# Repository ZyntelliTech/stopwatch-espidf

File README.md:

# Stopwatch ESP-IDF Project

This project implements a stopwatch using ESP-IDF on an ESP32 microcontroller with an OLED display.
## Hardware Architecture
The ESP32-S3 GPIO pins have been assigned as follows: 

GPIO12 ------> SCL <br>
GPIO11 ------> SDA <br> 
GPIO10 ------> CS <br>
GPIO9  ------> DC<br>
GPIO8  ------> RES<br>

GPIO5  ------> left button: Start/Stop <br>
GPIOP6 ------> middle button: lapping/page navigation <br>
GPIO7  ------> right button: reset<br>

You can check the details in the schematic.

### How to order prototypes in JLCPCB
- Go to jlcpcb.com
- Click "Order now"
- Click "Add Gerber file" and upload /Hardware/Gerber_xxxxxxx.zip file
- Select the PCB Qty
- Enable the PCB Assembly
- Choose the Standard and Top Side assembly
- Click the NEXT button in the right panel. You will go to the next page
- Add the BOM and CPL(Pick-and-Place) files from hardware directory
- You can check the component stocks in the list
- In the Component Placements, you can check the assembled board.
- You can check the price in the Quote & Order page and save to cart

## Firmware Development

### Prerequisites

- [Visual Studio Code](https://code.visualstudio.com/)
- ESP32 development board (e.g., ESP32-S3)
- USB cable for flashing

### Installing ESP-IDF in VS Code

Follow these steps to set up the ESP-IDF development environment in Visual Studio Code. [Refer to this link.](https://www.youtube.com/watch?v=D0fRc4XHBNk) 

### 1. Install Visual Studio Code
If you haven't already, download and install VS Code from the official website.

### 2. Install the ESP-IDF Extension
1. Open VS Code.
2. Go to the Extensions view by clicking on the Extensions icon in the Activity Bar on the side of the window (or press `Ctrl+Shift+X`).
3. Search for "ESP-IDF".
4. Find the extension published by "Espressif Systems" and click "Install".

### 3. Open the Project
1. Open VS Code.
2. Select "File" > "Open Folder" and navigate to the `stopwatch-espidf/Firmware` directory.

### 4. Build and Flash the Project
1. In VS Code, open the Command Palette (`Ctrl+Shift+P`).
2. Type "ESP-IDF: Open ESP-IDF Terminal" and click it
3. Run "idf.py build".
4. Connect your ESP32 board via USB.
5. Run "idf.py flash monitor" to flash the firmware.
6. Optionally, run "idf.py -p COM[X] flash monitor" if the COM port is not automatically selected

## Project Structure

- `Firmware/`: Contains the ESP-IDF project files.
- `Firmware/main/`: Source code for the stopwatch application.
- `Firmware/components/`: Additional components like u8g2 for OLED display.
- `images/`: Project images like testing board diagram

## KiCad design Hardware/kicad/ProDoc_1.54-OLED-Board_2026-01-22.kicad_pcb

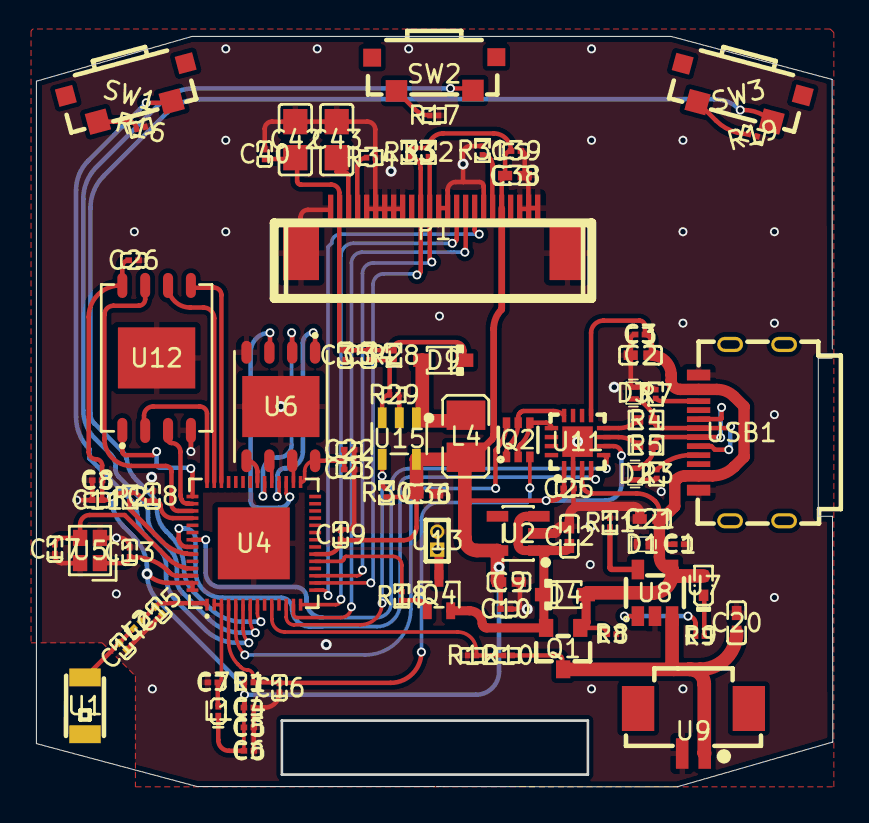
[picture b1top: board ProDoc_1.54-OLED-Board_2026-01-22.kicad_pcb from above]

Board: 2 copper layers, 44.2 x 41.7 mm, 83 parts (0 on the bottom side), 61 nets.

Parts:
C1: 2.2uF; C0201
C2, C9, C12, C20, C21, C36, C38: 10uF; C0402
C3, C4, C6, C7, C8, C10, C11, C16, C18, C19, C22, C25, C26, C35, C39, C40: 100nF; C0201
C5, C23: 1uF; C0201
C13, C17: 15pF; C0201
C14: 1.8pF; C0201
C15: 1.2pF; C0201
C34: 22pF; C0201
C42, C43: 10uF; C0805
D1, D2, D3: LESD8LH5.0CT5G; SOD-882_L1.0-W0.6-BI
D4, D9: 1N5819WS_C191023; SOD-323_L1.8-W1.3-LS2.5-RD
L1: 2nH; L0201-RD
L2: 2.4nH; L0201
L4: 10uH; L1008
P1: FPC 0.5MM 24P Pull type H2.0mm Pick up; FPC-SMD_24P-L17.5-W5.4-P0.50
Q1: AO3401A_C347476; SOT-23_L2.9-W1.3-P1.90-LS2.4-BR
Q2: UMH3N; SC-70-6_L2.2-W1.3-P0.65-LS2.1-BR
Q4: SS8550W; SOT-323-3_L2.0-W1.3-P1.30-LS2.3-BR
R1, R2, R16, R17, R19: 10kΩ; R0201
R3, R7: 5.1kΩ; R0201
R4, R5: 0Ω; R0402
R8, R29, R30: 100kΩ; R0201
R9: 1kΩ; R0201
R10, R12: 470kΩ; R0201
R11: 2kΩ; R0201
R18: 470Ω; R0201
R28: 887kΩ; R0201
R31, R32, R33: 4.7kΩ; R0201
R34: 910kΩ; R0201
SW1, SW2, SW3: TS36CA-0.6 250gf 031; SW-SMD_SHOU_TS36CA-0.6
U1: ANT3216LL00R2400A; ANT-SMD_L3.2-W1.6
U2: SPX3819M5-L-3-3; SOT-23-5_L3.0-W1.6-P0.95-LS2.8-BR
U4: ESP32-S3R8; QFN-56_L7.0-W7.0-P0.40-TL-EP4.0
U5: 40MHz; CRYSTAL-SMD_4P-L2.0-W1.6-BL
U6: W25Q128JVPIQ; WSON-8_L6.0-W5.0-P1.27-BL-EP
U7: XL-1005UOC; LED0402-RD_ORANGE
U8: TP4054_C668215; TSOT-23-5_L2.9-W1.6-P0.95-LS2.8-BR
U9: ZX-MX1.25-2PWT; CONN-SMD_2P-P1.25_MEGASTAR_ZX-MX1.25-2PWT
U11: CH343P; TQFN-16_L3.0-W3.0-P0.50-BL-EP1.7
U12: W25N01GVZEIG; WSON-8_L8.0-W6.10-P1.27-BL-EP
U13: HX PZ1.0-1x2P ZZ; HDR-TH_2P-P1.00-V-M
U15: TPS61040DBVR; SOT-23-5_L3.0-W1.7-P0.95-LS2.8-BL
USB1: HYCW412-USBC16-065B; USB-C-SMD_HYCW412-USBC16-065B

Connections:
5V: C1.1, C2.2, C3.2, C21.2, D1.1, D4.2, Q1.1, R8.1, U7.2, U8.4, U11.3, U11.9, USB1.A4B9, USB1.B4A9
12V: C34.2, C35.2, C40.2, C42.2, D9.1, P1.23, R28.2
$1N9431: C15.2, L2.2, U4.1
$1N9432: C7.2, L1.2, U4.2, U4.3
$1N9438: C13.1, U4.54, U5.1
$1N9473: C17.2, U4.53, U5.3
$1N9512: R9.1, U7.1
$1N9513: R9.2, U8.1
$1N9514: R11.1, U8.5
$1N9533: R16.1, SW1.1
$1N9534: R17.1, SW2.1
$1N9535: R19.1, SW3.1
$1N9548: Q4.1, R18.2
$1N9549: Q4.3, U13.1
$1N9587: C14.2, L2.1, U1.2
$1N9591: R7.2, USB1.B5
$1N9592: R3.1, USB1.A5
$1N9604: P1.6, R31.2
$1N9614: D9.2, L4.2, U15.1
$1N9616: C34.1, R28.1, R29.2, U15.3
$1N9620: P1.21, R34.2
$1N9621: C43.2, P1.22
+3V3: C4.2, C5.2, C6.2, C8.2, C9.2, C10.2, C11.2, C18.2, C19.2, C25.2, C26.2, C36.2, C38.1, C39.1, L1.1, L4.1, P1.5, R1.2, R2.2, R30.2, R32.1, R33.1, U2.5, U4.20, U4.46, U4.55, U4.56, U11.1, U11.6, U12.8, U15.5
BAT_ADC: R10.1, R12.2, U4.10
BUZZER: R18.1, U4.19
CHIP_EN: C16.2, Q2.3, R1.1, U4.4
CLK: P1.13, R32.2, U4.17
CS: P1.8, U4.15
D+: R5.1, U11.7
D-: R4.1, U11.8
DC: P1.10, U4.14
DIN: P1.14, R33.2, U4.16
DTR: Q2.1, Q2.5, U11.12
EN: R30.1, U4.12, U15.4
FCLK: U4.41, U12.6
FCS: U4.43, U12.1
FDI: U4.40, U12.5
FDO: U4.42, U12.2
FHOLD: U4.45, U12.7
FWP: U4.44, U12.3
GND: C1.2, C2.1, C3.1, C4.1, C5.1, C6.1, C7.1, C8.1, C9.1, C10.1, C11.1, C12.1, C13.2, C14.1, C15.1, C16.1, C17.1, C18.1, C19.1, C20.1, C21.1, C22.1, C23.1, C25.1, C26.1, C35.1, C36.1, C38.2, C39.2, C40.1, C42.1, C43.1, D1.2, D2.2, D3.1, P1.1, P1.2, P1.3, P1.7, P1.11, P1.12, P1.16, P1.17, P1.18, P1.19, P1.20, P1.24, P1.25, P1.26, R3.2, R7.1, R8.2, R11.2, R12.1, R16.2, R17.2, R19.2, R29.1, R31.1, R34.1, U2.2, U4.57, U5.2, U5.4, U6.4, U6.9, U8.2, U9.2, U11.2, U11.17, U12.4, U12.9, U13.2, U15.2, USB1.A1B12, USB1.B1A12
IO0: Q2.6, U4.5
IO45: R2.1, U4.51
KEY1: SW1.2, U4.6
KEY2: SW2.2, U4.7
KEY3: SW3.2, U4.8
RES: P1.9, U4.13
RTS: Q2.2, Q2.4, U11.13
SPICLK: U4.33, U6.6
SPICS0: U4.32, U6.1
SPID: U4.35, U6.5
SPIHD: U4.30, U6.7
SPIQ: U4.34, U6.2
SPIWP: U4.31, U6.3
U0RXD: U4.50, U11.4
U0TXD: U4.49, U11.5
USB+: D2.1, R5.2, USB1.A6, USB1.B6
USB-: D3.2, R4.2, USB1.A7, USB1.B7
VBAT: C20.2, Q1.3, R10.2, U8.3, U9.1
VDD_SPI: C22.2, C23.2, U4.29, U6.8
VSYS: C12.2, D4.1, Q1.2, Q4.2, U2.1, U2.3

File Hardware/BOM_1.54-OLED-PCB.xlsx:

No. | Quantity | Comment | Designator | Footprint | Value | Manufacturer Part | Manufacturer | Supplier Part 1 | Supplier 1 | Supplier Part 2 | Supplier 2 | LCSC Stock | LCSC Price | JLCPCB Stock | JLCPCB Price
1 | 1 | 2.2uF | C1 | C0201 | 2.2uF | CL03A225MP3CRNC | SAMSUNG(三星) |  |  | C318539 | LCSC |  |  | 350876 | 0.0011
2 | 7 | 10uF | C2,C9,C12,C20,C21,C36,C38 | C0402 | 10uF | CL05A106MP5NUNC | SAMSUNG(三星) |  |  | C315248 | LCSC |  |  | 4072911 | 0.0013
3 | 14 | 100nF | C3,C4,C6,C7,C8,C10,C11,C16,C18,C19,C22,C25,C26,C39 | C0201 | 100nF | GRM033R61A104KE15D | muRata(村田) |  |  | C76934 | LCSC |  |  | 5535950 | 0.0002
4 | 2 | 1uF | C5,C23 | C0201 | 1uF | HGC0201R5105K100NTCJ | Chinocera(华瓷) |  |  | C7432760 | LCSC |  |  | 68417 | 0.0015
5 | 2 | 15pF | C13,C17 | C0201 | 15pF | CC0201FRNPO9BN150 | YAGEO(国巨) |  |  | C541259 | LCSC |  |  | 8525 | 0.0005
6 | 1 | 1.8pF | C14 | C0201 | 1.8pF | GRM0335C1H1R8BA01D | muRata(村田) |  |  | C161415 | LCSC |  |  | 31014 | 0.0005
7 | 1 | 1.2pF | C15 | C0201 | 1.2pF | GRM0335C1H1R2BA01D | muRata(村田) |  |  | C85895 | LCSC |  |  | 426669 | 0.0005
8 | 1 | 22pF | C34 | C0201 | 22pF | CC0201JRNPO8BN220 | YAGEO(国巨) |  |  | C526934 | LCSC |  |  | 9722 | 0.0002
9 | 2 | 100nF | C35,C40 | C0201 | 100nF | CC0201KRX5R8BB104 | YAGEO(国巨) |  |  | C718252 | LCSC |  |  | 248761 | 0.0006
10 | 2 | 10uF | C42,C43 | C0805 | 10uF | CL21A106KAYNNNE | SAMSUNG(三星) |  |  | C15850 | LCSC |  |  | 2623875 | 0.0019
11 | 3 | LESD8LH5.0CT5G | D1,D2,D3 | SOD-882_L1.0-W0.6-BI |  | LESD8LH5.0CT5G | LRC(乐山无线电) |  |  | C172420 | LCSC |  |  | 13907 | 0.0023
12 | 2 | 1N5819WS | D4,D9 | SOD-323_L1.8-W1.3-LS2.5-RD |  | 1N5819WS | Hottech(合科泰) |  |  | C191023 | LCSC |  |  | 2805644 | 0.0015
13 | 1 | 2nH | L1 | L0603 | 2nH | VHF160808H2N0ST | FH(风华) |  |  | C395081 | LCSC |  |  | 16418 | 0.0012
14 | 1 | 2.4nH | L2 | L0201 | 2.4nH | LQP03TN2N4B02D | muRata(村田) |  |  | C98042 | LCSC |  |  | 98414 | 0.0008
15 | 1 | 10uH | L4 | L1008 | 10uH | MLP2520S100ST0S1 | TDK |  |  | C2049757 | LCSC |  |  | 3298 | 0.0157
16 | 1 | FPC 0.5MM 24P Pull type H2.0mm Pick up | P1 | FPC-SMD_24P-L17.5-W5.4-P0.50 |  | FPC 0.5MM 24P Pull type H2.0mm Pick up | ReliaPro |  |  | C11092 | LCSC |  |  | 12306 | 0.0135
17 | 1 | AO3401A | Q1 | SOT-23_L2.9-W1.3-P1.90-LS2.4-BR |  | AO3401A | UMW(友台半导体) |  |  | C347476 | LCSC |  |  | 1130408 | 0.0046
18 | 1 | UMH3N | Q2 | SC-70-6_L2.2-W1.3-P0.65-LS2.1-BR |  | UMH3N | CJ(江苏长电/长晶) |  |  | C62892 | LCSC |  |  | 27558 | 0.0073
19 | 1 | SS8550W | Q4 | SOT-323-3_L2.0-W1.3-P1.30-LS2.3-BR |  | SS8550W | TWGMC(迪嘉) |  |  | C5189253 | LCSC |  |  | 8957 | 0.0027
20 | 5 | 10kΩ | R1,R2,R16,R17,R19 | R0201 | 10kΩ | 0201WMF1002TEE | UNI-ROYAL(厚声) |  |  | C473048 | LCSC |  |  | 145236 | 0.0002
21 | 2 | 5.1kΩ | R3,R7 | R0201 | 5.1kΩ | 0201WMF5101TEE | UNI-ROYAL(厚声) |  |  | C270344 | LCSC |  |  | 9312 | 0.0002
22 | 2 | 0Ω | R4,R5 | R0402 | 0Ω | RC0402FR-070RL | YAGEO(国巨) |  |  | C106231 | LCSC |  |  | 1124117 | 0.0002
23 | 3 | 100kΩ | R8,R29,R30 | R0201 | 100kΩ | 0201WMF1003TEE | UNI-ROYAL(厚声) |  |  | C270364 | LCSC |  |  | 2651694 | 0.0002
24 | 1 | 1kΩ | R9 | R0201 | 1kΩ | 0201WMF1001TEE | UNI-ROYAL(厚声) |  |  | C270365 | LCSC |  |  | 1692718 | 0.0002
25 | 2 | 470kΩ | R10,R12 | R0201 | 470kΩ | 0201WMF4703TEE | UNI-ROYAL(厚声) |  |  | C473560 | LCSC |  |  | 9873 | 0.0002
26 | 1 | 2kΩ | R11 | R0201 | 2kΩ | 0201WMF2001TEE | UNI-ROYAL(厚声) |  |  | C270358 | LCSC |  |  | 167177 | 0.0002
27 | 1 | 470Ω | R18 | R0201 | 470Ω | 0201WMF4700TEE | UNI-ROYAL(厚声) |  |  | C473464 | LCSC |  |  | 138902 | 0.0002
28 | 1 | 887kΩ | R28 | R0201 | 887kΩ | RC0201FR-07887KL | YAGEO(国巨) |  |  | C474853 | LCSC |  |  | 4770 | 0.0002
29 | 3 | 4.7kΩ | R31,R32,R33 | R0201 | 4.7kΩ | 0201WMF4701TEE | UNI-ROYAL(厚声) |  |  | C270346 | LCSC |  |  | 62085 | 0.0002
30 | 1 | 910kΩ | R34 | R0201 | 910kΩ | RC0201FR-07910KL | YAGEO(国巨) |  |  | C295818 | LCSC |  |  | 8004 | 0.0002
31 | 3 | TS36CA-0.6 250gf 031 | SW1,SW2,SW3 | SW-SMD_SHOU_TS36CA-0.6 |  | TS36CA-0.6 250gf 031 | SHOU HAN(首韩) |  |  | C2906288 | LCSC |  |  | 48645 | 0.0037
32 | 1 | ANT3216LL00R2400A | U1 | ANT-SMD_L3.2-W1.6 |  | ANT3216LL00R2400A | YAGEO(国巨) |  |  | C293767 | LCSC |  |  | 22045 | 0.0156
33 | 1 | SPX3819M5-L-3-3 | U2 | SOT-23-5_L3.0-W1.6-P0.95-LS2.8-BR |  | SPX3819M5-L-3-3 | TECH PUBLIC(台舟) |  |  | C20617301 | LCSC |  |  | 48457 | 0.0144
34 | 1 | ESP32-S3R8 | U4 | QFN-56_L7.0-W7.0-P0.40-TL-EP4.0 |  | ESP32-S3R8 | ESPRESSIF(乐鑫) |  |  | C2913194 | LCSC |  |  | 8360 | 0.482
35 | 1 | 40MHz | U5 | CRYSTAL-SMD_4P-L2.0-W1.6-BL | 40MHz | TAXM40M4ZHBCDT2T | YJX(雅晶鑫) |  |  | C424432 | LCSC |  |  | 37872 | 0.0104
36 | 1 | W25Q128JVPIQ | U6 | WSON-8_L6.0-W5.0-P1.27-BL-EP |  | W25Q128JVPIQ | Winbond(华邦) |  |  | C190862 | LCSC |  |  | 12926 | 0.2921
37 | 1 | XL-1005UOC | U7 | LED0402-RD_ORANGE |  | XL-1005UOC | XINGLIGHT(成兴光) |  |  | C965791 | LCSC |  |  | 66096 | 0.002
38 | 1 | TP4054 | U8 | TSOT-23-5_L2.9-W1.6-P0.95-LS2.8-BR |  | TP4054 | UMW(友台半导体) |  |  | C668215 | LCSC |  |  | 244495 | 0.0054
39 | 1 | ZX-MX1.25-2PWT | U9 | CONN-SMD_2P-P1.25_MEGASTAR_ZX-MX1.25-2PWT |  | ZX-MX1.25-2PWT | Megastar(兆星) |  |  | C7430468 | LCSC |  |  | 79879 | 0.0042
40 | 1 | CH343P | U11 | TQFN-16_L3.0-W3.0-P0.50-BL-EP1.7 |  | CH343P | WCH(南京沁恒) |  |  | C2846043 | LCSC |  |  | 7491 | 0.1689
41 | 1 | W25N01GVZEIG | U12 | WSON-8_L8.0-W6.10-P1.27-BL-EP |  | W25N01GVZEIG | Winbond(华邦) |  |  | C907680 | LCSC |  |  | 7972 | 0.9838
42 | 1 | HX PZ1.0-1x2P ZZ | U13 | HDR-TH_2P-P1.00-V-M |  | HX PZ1.0-1x2P ZZ | hanxia(韩下) |  |  | C22438170 | LCSC |  |  | 6059 | 0.0047
43 | 1 | TPS61040DBVR | U15 | SOT-23-5_L3.0-W1.7-P0.95-LS2.8-BL |  | TPS61040DBVR | TI(德州仪器) |  |  | C7722 | LCSC |  |  | 54105 | 0.0339
44 | 1 | HYCW412-USBC16-065B | USB1 | USB-C-SMD_HYCW412-USBC16-065B |  | HYCW412-USBC16-065B | 华宇创 |  |  | C5342196 | LCSC |  |  | 2916 | 0.0853

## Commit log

2026-01-14 finished stopwatch screen
2026-01-14 remove submodules
2026-01-14 Add custom components
2026-01-19 Add fabrication files
2026-01-19 Add block diagram
2026-01-29 update confirming page
2026-01-29 Update fabrication files
